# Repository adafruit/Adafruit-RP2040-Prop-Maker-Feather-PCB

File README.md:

## Adafruit RP2040 Prop-Maker Feather with I2S Audio Amplifier PCB

<a href="http://www.adafruit.com/products/5768"><br/>
Click here to purchase one from the Adafruit shop</a>

PCB files for the Adafruit RP2040 Prop-Maker Feather with I2S Audio Amplifier. 

Format is EagleCAD schematic and board layout
* https://www.adafruit.com/product/5768

### Description

The Adafruit Feather series gives you lots of options for a small, portable, rechargeable microcontroller board. By picking a feather and stacking on a FeatherWing you can create advanced projects quickly. One popular combo is our Feather M4 or Feather RP2040 with a Prop-Maker FeatherWing on top to create animatronics or props that boot up instantly and can drive LEDs, and small speakers.

We've used the Prop-Maker FeatherWing to make lots of lil robots, swords, and other prop projects. However, what if we made it even easier for people to make props? What if we made it so many projects can be built with minimal or no soldering at all? Yeah that would be pretty nice!

Thus, the creation of the Feather P2040 Prop-Maker: an all-in-one combination of the Feather RP2040 with a Prop-Maker FeatherWing with a few tweaks based on feedback from expert prop-builders. Perfect for fitting into your next prop build! This Feather will unlock the prop-maker inside all of us, with tons of stuff packed in to make sabers & swords, props, toys, cosplay pieces, and more.

We looked at hundreds of prop builds, and thought about what would make for a great low-cost (but well-designed) add-on for our Feather boards. Here's what we came up with:

* Terminal Block NeoPixel Port - With easy-to-use screw terminals you can quickly connect and disconnect your NeoPixel strips and rings. This port provides high current drive from either the Feather Lipoly or USB port, whichever is higher. A 5V level up-shifter gives you a clean voltage signal to reduce glitchiness no matter what chip you're using. You can also cut power to the entire strip instantly to reduce quiescent power, thanks to a separate control transistor.
* MAX98357 I2S 3 Watt Class D Audio Amplifier - Drive any 4-8Ω speaker, up to 3 Watts, for sound effects. Audio comes out on two of the terminal blocks so you can screw in any wires to a speaker you like - we're partial to this small 3W speaker with pre-attached wires. Thanks to the I2S digital inputs, you'll get excellent audio quality
* Triple-Axis Accelerometer with Tap Detection - The LIS3DH is our favorite accelerometer, you can use this for detection motion, tilt, or taps. Here's an example of a lightsaber that makes sounds when swung or hit. We have code for this chip in both Arduino and CircuitPython.
* Extra Button or Output Pin - One more pin on the terminal screw block can be used for button input or digital output, for activation or a simple LED.
* Servo Connection - Plug any hobby servo with 3 wires into the 0.1" spaced header, and you can have quick motion control.
* Low power mode! The power system for the NeoPixels and speaker amplifier can be controlled by a pin to cut power to them, so you have lower power usage when the prop is in sleep or off mode (but can wake up fast by listening to the button press or accelerometer data).

At the Feather's heart is an RP2040 chip, clocked at 133 MHz and at 3.3V logic, the same one used in the Raspberry Pi Pico. This chip has a whopping 8 MB of onboard QSPI FLASH and 264K of RAM!  There's even room left over for a STEMMA QT connector for plug-and-play of I2C devices.

To make it easy to use for portable projects, we added a connector for any of our 3.7V Lithium polymer batteries and built in battery charging. You don't need a battery, it will run just fine straight from the USB Type C connector. But, if you do have a battery, you can take it on the go, then plug in the USB to recharge. The Feather will automatically switch over to USB power when it's available.

Here're some handy specs! You get:

* Measures 52.1mm x 22.8mm x 12.2mm / 2.1" x 0.9" x 0.5 without headers soldered in
* Light as a (large?) feather - ~7grams
* RP2040 32-bit Cortex M0+ dual core running at ~133 MHz @ 3.3V logic and power
* 264 KB RAM
* 8 MB SPI FLASH chip for storing files, images, and CircuitPython/MicroPython code storage. No EEPROM
* Tons of GPIO! 21 x GPIO pins with following capabilities:
	* Four 12-bit ADCs (one more than Pico)
	* Two I2C, Two SPI, and two UART peripherals, we label one for the 'main' interface in standard Feather locations
	* 16 x PWM outputs - for servos, LEDs, etc
* Built-in 200mA+ lipoly charger with charging status indicator LED
* Pin #13 red LED for general purpose blinking
* RGB NeoPixel for full-color indication.
* On-board STEMMA QT connector that lets you quickly connect any Qwiic, STEMMA QT or Grove I2C devices with no soldering!
* Both Reset button and Bootloader select button for quick restarts (no unplugging-replugging to relaunch code)
* USB Type C connector lets you access built-in ROM USB bootloader and serial port debugging
* 3.3V regulator with 500mA peak current output and power enable pin
* 4 mounting holes
* 12 MHz crystal for perfect timing.
* Prop-Making section with I2S 3W audio amplifier, 5V NeoPixel level shifting, accelerometer, servo port, and terminal blocks for fast solder-free connections.

Comes assembled and tested, with some header. You'll need a soldering iron to attach the header if you'd like to use it on a breadboard!

### License

Adafruit invests time and resources providing this open source design, please support Adafruit and open-source hardware by purchasing products from [Adafruit](https://www.adafruit.com)!

Designed by Limor Fried/Ladyada for Adafruit Industries.

Creative Commons Attribution/Share-Alike, all text above must be included in any redistribution. 
See license.txt for additional details.

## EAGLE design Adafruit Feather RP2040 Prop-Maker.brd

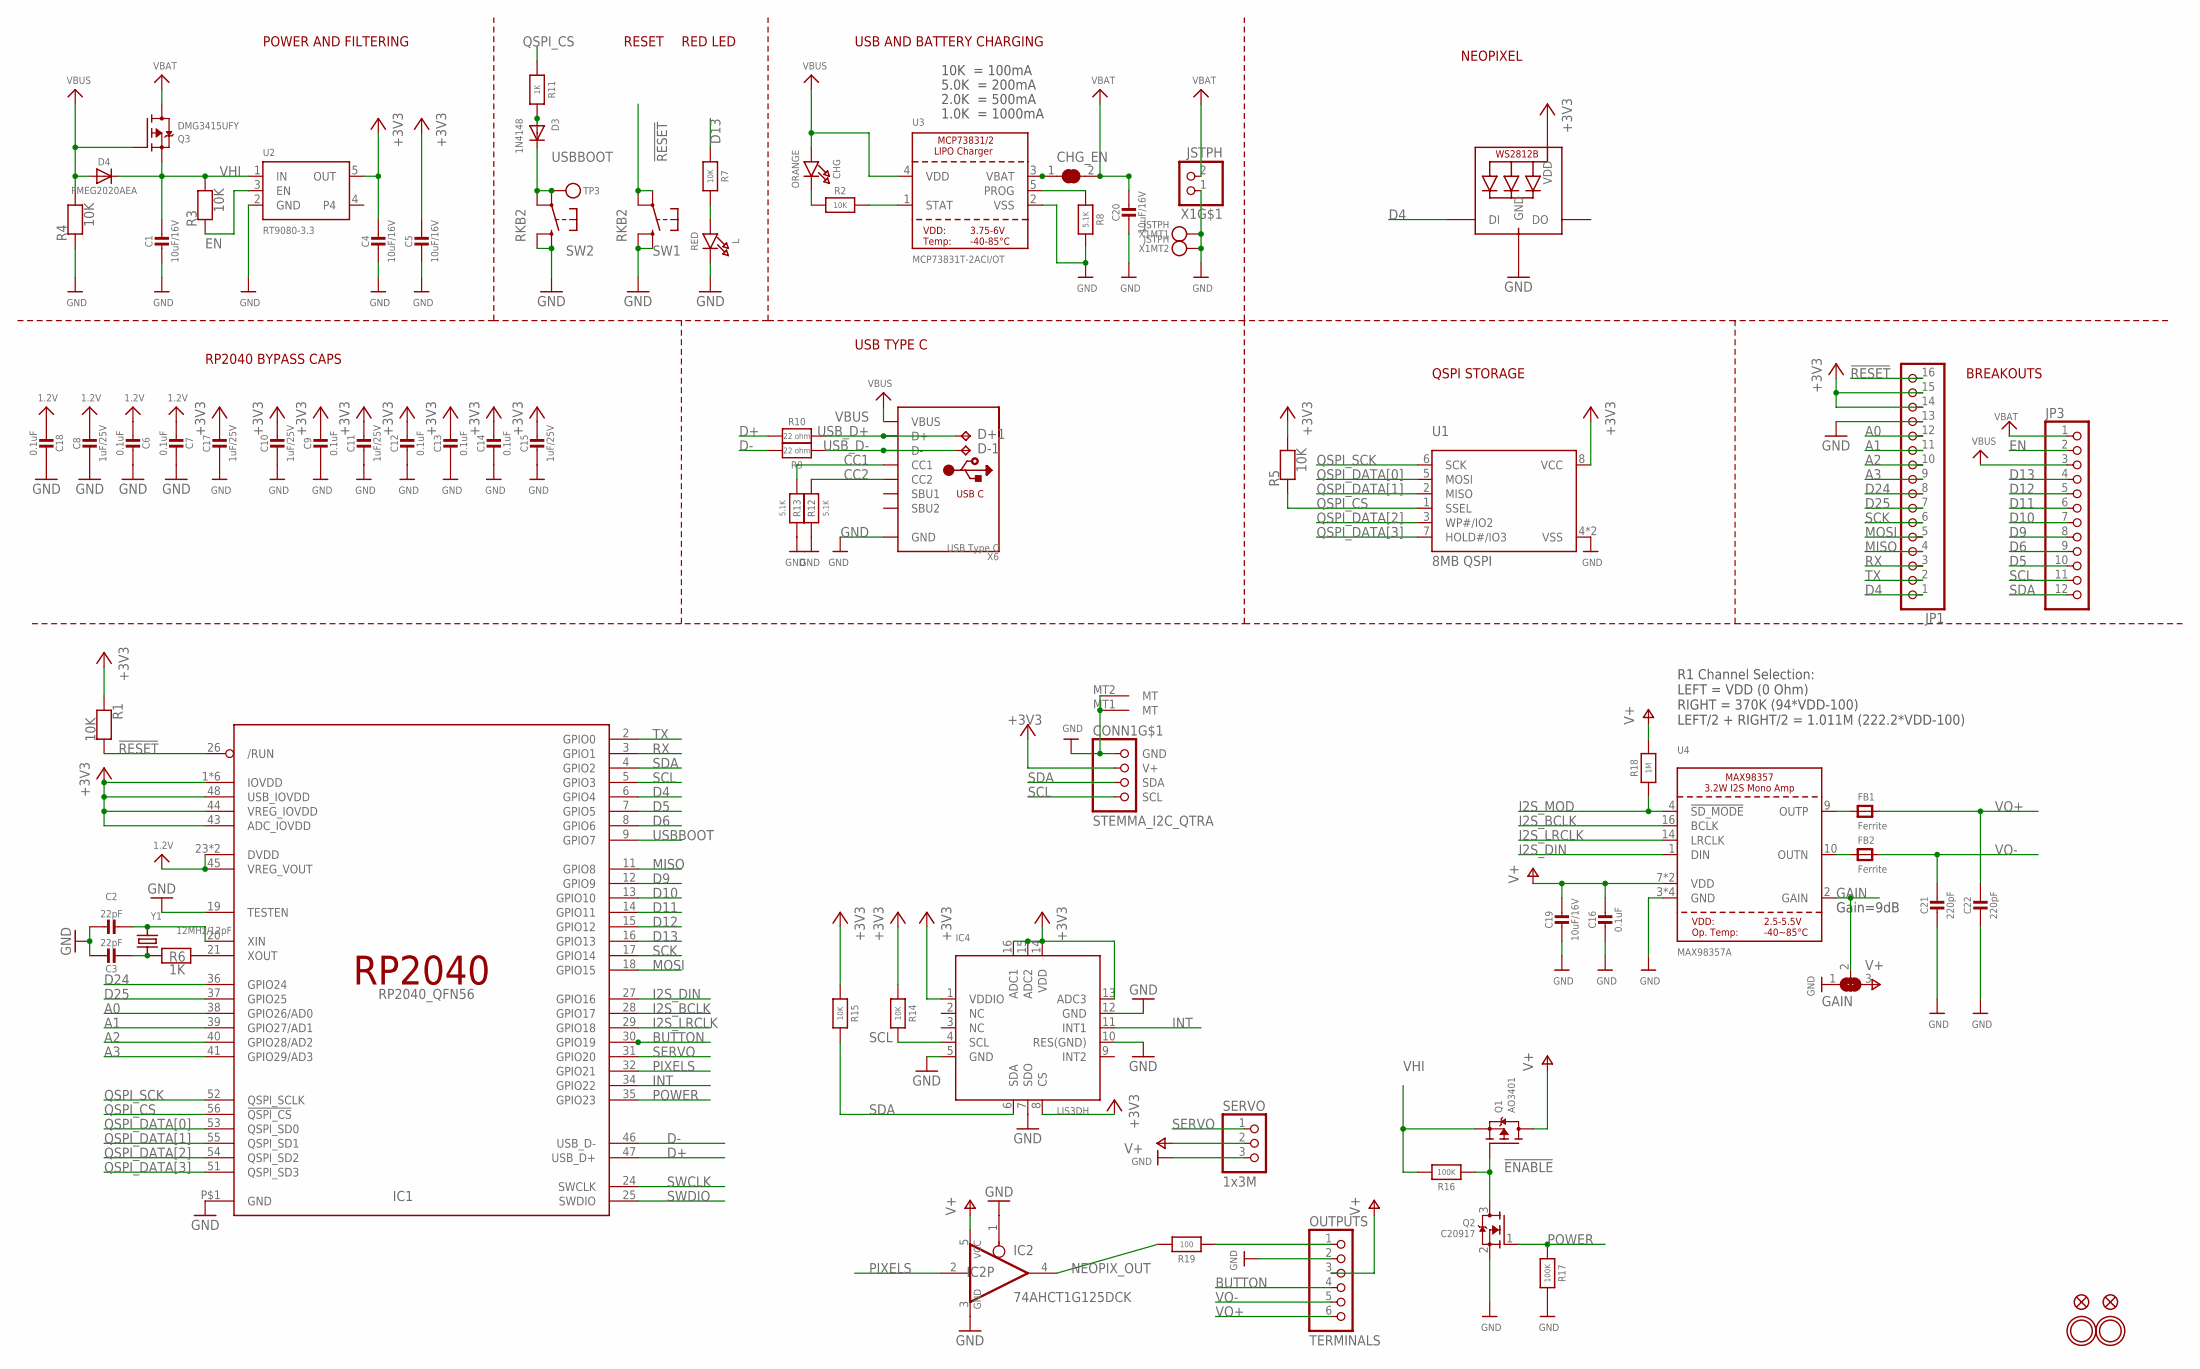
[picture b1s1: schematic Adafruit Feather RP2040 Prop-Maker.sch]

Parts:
C1, C4, C5, C19, C20: 10uF/16V; 0805-NO
C2, C3: 22pF; _0402NO
C6, C7, C9, C12, C13, C14, C16, C18: 0.1uF; _0402NO
C8, C10, C11, C15, C17: 1uF/25V; _0402NO
C21, C22: 220pF; _0402NO
CHG: ORANGE; CHIPLED_0603_NOOUTLINE
CHG_EN: SOLDERJUMPER_CLOSED; SOLDERJUMPER_CLOSEDWIRE
CONN1: STEMMA_I2C_QTRA; JST_SH4_RA
D3: 1N4148; SOD-323_MINI
D4: PMEG2020AEA; SOD-323F
D+1: TPB1,27; B1,27
D-1: TPB1,27; B1,27
FB1, FB2: Ferrite; 0603-NO
GAIN: SOLDERJUMPER_2WAY; SOLDERJUMPER_2WAY_OPEN_NOPASTE
IC1: RP2040_QFN56; QFN56_7MM_REDUCEDEPAD
IC2: 74AHCT1G125DCK; SC70-5
IC4: LIS3DH; LGA16_3X3MM
JP1: HEADER-1X16ROUND; 1X16_ROUND
JP3: HEADER-1X12; 1X12_ROUND
L: RED; CHIPLED_0603_NOOUTLINE
LED1: WS2812B_SK6805_1515; SK6805_1515
OUTPUTS: TERMINALS; 1X06_OVAL
Q1: AO3401; SOT23-WIDE
Q2: C20917; SOT23-WIDE
Q3: DMG3415UFY; DFN2015-3
R1, R2, R3, R4, R5, R7, R14, R15: 10K; _0402NO
R6, R11: 1K; _0402NO
R8, R12, R13: 5.1K; _0402NO
R9, R10: 22 ohm; _0402NO
R16, R17: 100K; _0402NO
R18: 1M; _0402NO
R19: 100; _0402NO
SERVO: 1x3M; 1X03_ROUND_76
SW1, SW2: RKB2; BTN_RKB2_4.6X2.8
TP3: TESTPOINTROUND1.5MMNO; TESTPOINT_ROUND_1.5MM_NO
U1: 8MB QSPI; USON8_4X4
U2: RT9080-3.3; SOT23-5; JLC_ROTATION 0
U3: MCP73831T-2ACI/OT; SOT23-5; JLC_ROTATION 0
U4: MAX98357A; QFN16_3MM
U$31, U$32: MOUNTINGHOLE2.5; MOUNTINGHOLE_2.5_PLATED
U$34, U$35: FIDUCIAL_1MM
X1: JSTPH; JSTPH2_BATT
X6: USB Type C; USB_C_CUSB31-CFM2AX-01-X
Y1: 12MHz/12pF; CRYSTAL_2.5X2

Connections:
1.2V: C6.2, C7.2, C8.1, C18.2, IC1.23 (DVDD), IC1.45 (VREG_VOUT), IC1.50 (DVDD)
!ENABLE: Q1.1 (G), Q2.3 (D), R16.1
!RESET: IC1.26 (/RUN), JP1.16, R1.2, SW1.A, SW1.A' (P1)
+3V3: C4.1, C5.1, C9.1, C10.1, C11.1, C12.1, C13.1, C14.1, C15.1, C17.1, CONN1.2 (V+), IC1.1 (IOVDD), IC1.10 (IOVDD), IC1.22 (IOVDD), IC1.33 (IOVDD), IC1.42 (IOVDD), IC1.43 (ADC_IOVDD), IC1.44 (VREG_IOVDD), IC1.48 (USB_IOVDD), IC1.49 (IOVDD), IC4.1 (VDDIO), IC4.8 (CS), IC4.13 (ADC3), IC4.14 (VDD), IC4.15 (ADC2), IC4.16 (ADC1), JP1.14, JP1.15, LED1.2 (VDD), R1.1, R5.2, R14.1, R15.1, U1.8 (VCC), U2.5 (OUT)
A0: IC1.38 (GPIO26/AD0), JP1.12
A1: IC1.39 (GPIO27/AD1), JP1.11
A2: IC1.40 (GPIO28/AD2), JP1.10
A3: IC1.41 (GPIO29/AD3), JP1.9
BUTTON: IC1.30 (GPIO19), OUTPUTS.4
CC1: R13.2, X6.A5 (CC1)
CC2: R12.2, X6.B5 (CC2)
D4: IC1.6 (GPIO4), JP1.1, LED1.1 (DI)
D5: IC1.7 (GPIO5), JP3.10
D6: IC1.8 (GPIO6), JP3.9
D9: IC1.12 (GPIO9), JP3.8
D10: IC1.13 (GPIO10), JP3.7
D11: IC1.14 (GPIO11), JP3.6
D12: IC1.15 (GPIO12), JP3.5
D13: IC1.16 (GPIO13), JP3.4, R7.1
D24: IC1.36 (GPIO24), JP1.8
D25: IC1.37 (GPIO25), JP1.7
D+: IC1.47 (USB_D+), R10.2
D-: IC1.46 (USB_D-), R9.2
EN: JP3.2, R3.1, U2.3 (EN)
GAIN: GAIN.2, U4.2 (GAIN)
GND: C1.2, C2.1, C3.1, C4.2, C5.2, C6.1, C7.1, C8.2, C9.2, C10.2, C11.2, C12.2, C13.2, C14.2, C15.2, C16.2, C17.2, C18.1, C19.2, C20.2, C21.2, C22.2, CONN1.1 (GND), CONN1.MT1 (MT), CONN1.MT2 (MT), GAIN.1, IC1.19 (TESTEN), IC1.P$1 (GND), IC2.1 (OE), IC2.3 (GND), IC4.5 (GND), IC4.7 (SDO), IC4.10 (RES(GND)), IC4.12 (GND), JP1.13, L.C, LED1.4 (GND), OUTPUTS.2, Q2.2 (S), R4.1, R8.2, R12.1, R13.1, R17.2, SERVO.3, SW1.B (S), SW1.B' (S1), SW2.B (S), SW2.B' (S1), U1.4 (VSS), U1.PAD (VSS), U2.2 (GND), U3.2 (VSS), U4.3 (GND), U4.11 (GND), U4.15 (GND), U4.THERMAL (GND), X1.1, X1.NC1, X1.NC2, X6.A1B12 (GND), X6.B1A12 (GND)
I2S_BCLK: IC1.28 (GPIO17), U4.16 (BCLK)
I2S_DIN: IC1.27 (GPIO16), U4.1 (DIN)
I2S_LRCLK: IC1.29 (GPIO18), U4.14 (LRCLK)
I2S_MOD: R18.1, U4.4 (!SD_MODE)
INT: IC1.34 (GPIO22), IC4.11 (INT1)
MISO: IC1.11 (GPIO8), JP1.4
MOSI: IC1.18 (GPIO15), JP1.5
unnamed: CHG.C, R2.1
unnamed: L.A, R7.2
unnamed: R2.2, U3.1 (STAT)
unnamed: R8.1, U3.5 (PROG)
unnamed: C2.2, IC1.20 (XIN), Y1.3 (2)
unnamed: C3.2, R6.1, Y1.1
unnamed: IC1.21 (XOUT), R6.2
unnamed: FB2.1, U4.10 (OUTN)
unnamed: FB1.1, U4.9 (OUTP)
unnamed: CHG_EN.1, U3.3 (VBAT)
unnamed: D3.A, R11.2
NEOPIX_OUT: IC2.4 (O), R19.2
PIXELOUT: OUTPUTS.1, R19.1
PIXELS: IC1.32 (GPIO21), IC2.2 (I)
POWER: IC1.35 (GPIO23), Q2.1 (G), R17.1
QSPI_CS: IC1.56 (!QSPI_CS), R5.1, R11.1, U1.1 (SSEL)
QSPI_DATA[0]: IC1.53 (QSPI_SD0), U1.5 (MOSI)
QSPI_DATA[1]: IC1.55 (QSPI_SD1), U1.2 (MISO)
QSPI_DATA[2]: IC1.54 (QSPI_SD2), U1.3 (WP#/IO2)
QSPI_DATA[3]: IC1.51 (QSPI_SD3), U1.7 (HOLD#/IO3)
QSPI_SCK: IC1.52 (QSPI_SCLK), U1.6 (SCK)
RX: IC1.3 (GPIO1), JP1.3
SCK: IC1.17 (GPIO14), JP1.6
SCL: CONN1.4 (SCL), IC1.5 (GPIO3), IC4.4 (SCL), JP3.11, R14.2
SDA: CONN1.3 (SDA), IC1.4 (GPIO2), IC4.6 (SDA), JP3.12, R15.2
SERVO: IC1.31 (GPIO20), SERVO.1
SWCLK: IC1.24 (SWCLK)
SWDIO: IC1.25 (SWDIO)
TX: IC1.2 (GPIO0), JP1.2
USBBOOT: D3.C, IC1.9 (GPIO7), SW2.A, SW2.A' (P1), TP3.P$1
USB_D+: D+1.TP, R10.1, X6.A6 (D+), X6.B6 (D+)
USB_D-: D-1.TP, R9.1, X6.A7 (D-), X6.B7 (D-)
V+: C16.1, C19.1, GAIN.3, IC2.5 (VCC), OUTPUTS.3, Q1.3 (D), R18.2, SERVO.2, U4.7 (VDD), U4.8 (VDD)
VBAT: C20.1, CHG_EN.2, JP3.1, Q3.3 (D), X1.2
VBUS: CHG.A, D4.A, JP3.3, Q3.1 (G), R4.2, U3.4 (VDD), X6.A4B9 (VBUS), X6.B4A9 (VBUS)
VHI: C1.1, D4.C, Q1.2 (S), Q3.2 (S), R3.2, R16.2, U2.1 (IN)
VO+: C22.1, FB1.2, OUTPUTS.6
VO-: C21.1, FB2.2, OUTPUTS.5

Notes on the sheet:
POWER AND FILTERING
RESET
10K = 100mA
5.0K = 200mA
2.0K = 500mA
1.0K = 1000mA
USB AND BATTERY CHARGING
BREAKOUTS
RED LED
RP2040 BYPASS CAPS
USB TYPE C
QSPI STORAGE
NEOPIXEL
R1 Channel Selection: LEFT = VDD (0 Ohm) RIGHT = 370K (94*VDD-100) LEFT/2 + RIGHT/2 = 1.011M (222.2*VDD-100)
Gain=9dB

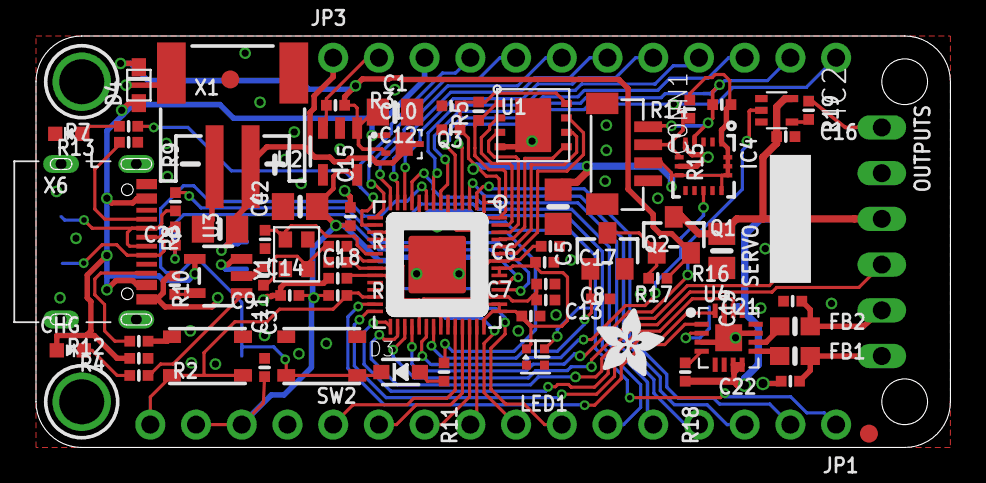
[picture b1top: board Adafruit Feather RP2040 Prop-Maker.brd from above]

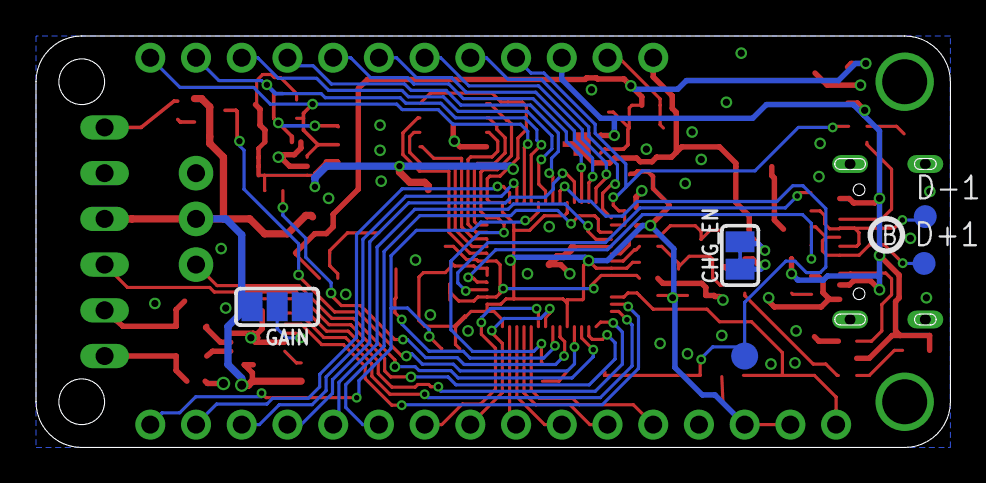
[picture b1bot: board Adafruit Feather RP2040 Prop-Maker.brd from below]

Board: 2 copper layers, 50.8 x 22.9 mm, 162 parts (51 on the bottom side), 69 nets.

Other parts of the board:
PLABEL0: PLABEL0
PLABEL1: PLABEL1
PLABEL2: PLABEL2
PLABEL3: PLABEL3
PLABEL4: PLABEL4
PLABEL5: PLABEL5
PLABEL6: PLABEL6
PLABEL7: PLABEL7
PLABEL8: PLABEL8
PLABEL9: PLABEL9
PLABEL10: PLABEL10
PLABEL11: PLABEL11
PLABEL12: PLABEL12
PLABEL13: PLABEL13
PLABEL14: PLABEL14
PLABEL15: PLABEL15
PLABEL16: PLABEL16
PLABEL17: PLABEL17
PLABEL18: PLABEL18
PLABEL19, PLABEL26: PLABEL26
PLABEL21: PLABEL21
PLABEL22: PLABEL22
PLABEL23: PLABEL23
PLABEL24: PLABEL24
PLABEL25: PLABEL25
PLABEL27: PLABEL27
PLABEL28: PLABEL28
PLABEL29: PLABEL29
PLABEL30: PLABEL30
PLABEL31: PLABEL31
PLABEL32: PLABEL32
PLABEL33: PLABEL33
PLABEL36: PLABEL36
PLABEL37: PLABEL37
PLABEL38: PLABEL38
PLABEL39: PLABEL39
PLABEL40: PLABEL40
PLABEL41: PLABEL41
PLABEL42: PLABEL42
PLABEL43: PLABEL43
PLABEL44: PLABEL44
PLABEL45: PLABEL45
PLABEL46: PLABEL46
PLABEL47: PLABEL47
PLABEL48: PLABEL48
PLABEL49: PLABEL49
PLABEL50: PLABEL50
PLABEL51: PLABEL51
PLABEL52: PLABEL52
PLABEL53: PLABEL53
PLABEL54: PLABEL54
PLABEL55: PLABEL55
PLABEL56: PLABEL56
PLABEL57: PLABEL57
PLABEL58: PLABEL58
PLABEL59: PLABEL59
PLABEL60: PLABEL60
PLABEL61: PLABEL61
PLABEL62: PLABEL62
PLABEL63: PLABEL63
PLABEL68: PLABEL68
PLABEL69: PLABEL69
PLABEL70: PLABEL70
PLABEL71: PLABEL71
PLABEL72: PLABEL72
PLABEL73: PLABEL73
PLABEL74: PLABEL74
PLABEL75: PLABEL75
PLABEL76: PLABEL76
PLABEL77: PLABEL77
PLABEL78: PLABEL78
PLABEL79: PLABEL79
PLABEL80: PLABEL80
PLABEL81: PLABEL81
PLABEL82: PLABEL82
PLABEL83: PLABEL83
PLABEL84: PLABEL84
PLABEL85: PLABEL85
PLABEL86: PLABEL86
PLABEL87: PLABEL87
PLABEL88: PLABEL88
PLABEL89: PLABEL89
U$13: PCBFEAT-REV-040
U$42: ADAFRUIT_3.5MM

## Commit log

2023-06-09 adding cookiecutter output
2023-06-09 adding prettypins
2023-06-09 adding factory reset
2023-06-13 updating prettypins
2023-06-19 updating factory reset
2023-06-19 adding new factory reset

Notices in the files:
parts and their libraries:
microbuilder: This work is placed in the public domain, and may be freely used for commercial and non-commercial work with the following conditions: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
